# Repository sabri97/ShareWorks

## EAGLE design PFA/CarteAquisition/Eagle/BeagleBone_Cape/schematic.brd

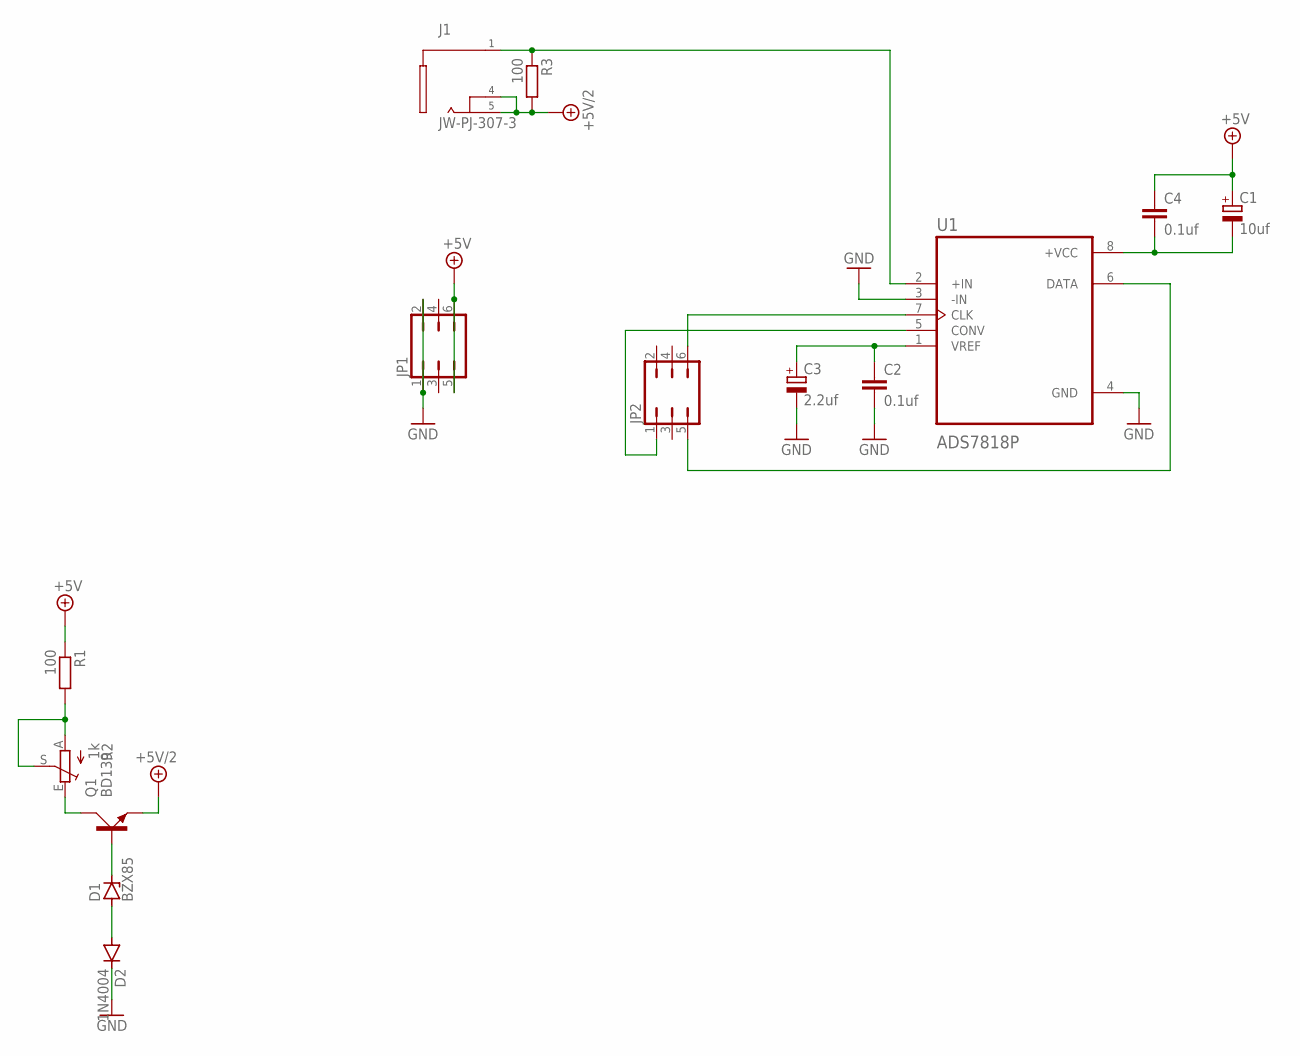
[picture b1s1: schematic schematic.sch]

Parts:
C1: 10uf; E3,5-8
C2, C4: 0.1uf; C050-030X075
C3: 2.2uf; E2,5-6
D1: BZX85; DO41Z10
D2: 1N4004; DO41-10
J1: JW-PJ-307-3; JW-PJ-307-X
JP1, JP2: JP3Q
Q1: BD139; TO126AV
R1, R3: 100; 0207/10
R2: 1k; CA9V
U1: ADS7818P; DIP794W45P254L959H508Q8

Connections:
+5V: C1.+, C4.1, JP1.5, JP1.6, R1.1
+5V/2: J1.P$4 (4), J1.P$5 (5), Q1.E, R3.2
GND: C2.2, C3.-, D2.C, JP1.1, JP1.2, U1.3 (-IN), U1.4 (GND)
unnamed: R1.2, R2.A, R2.S
unnamed: D1.A, D2.A
unnamed: D1.C, Q1.B
unnamed: Q1.C, R2.E
unnamed: JP2.6, U1.7 (CLK)
unnamed: J1.P$1 (1), R3.1, U1.2 (+IN)
unnamed: JP2.1, U1.5 (CONV)
unnamed: C2.1, C3.+, U1.1 (VREF)
unnamed: JP2.5, U1.6 (DATA)
unnamed: C1.-, C4.2, U1.8 (+VCC)

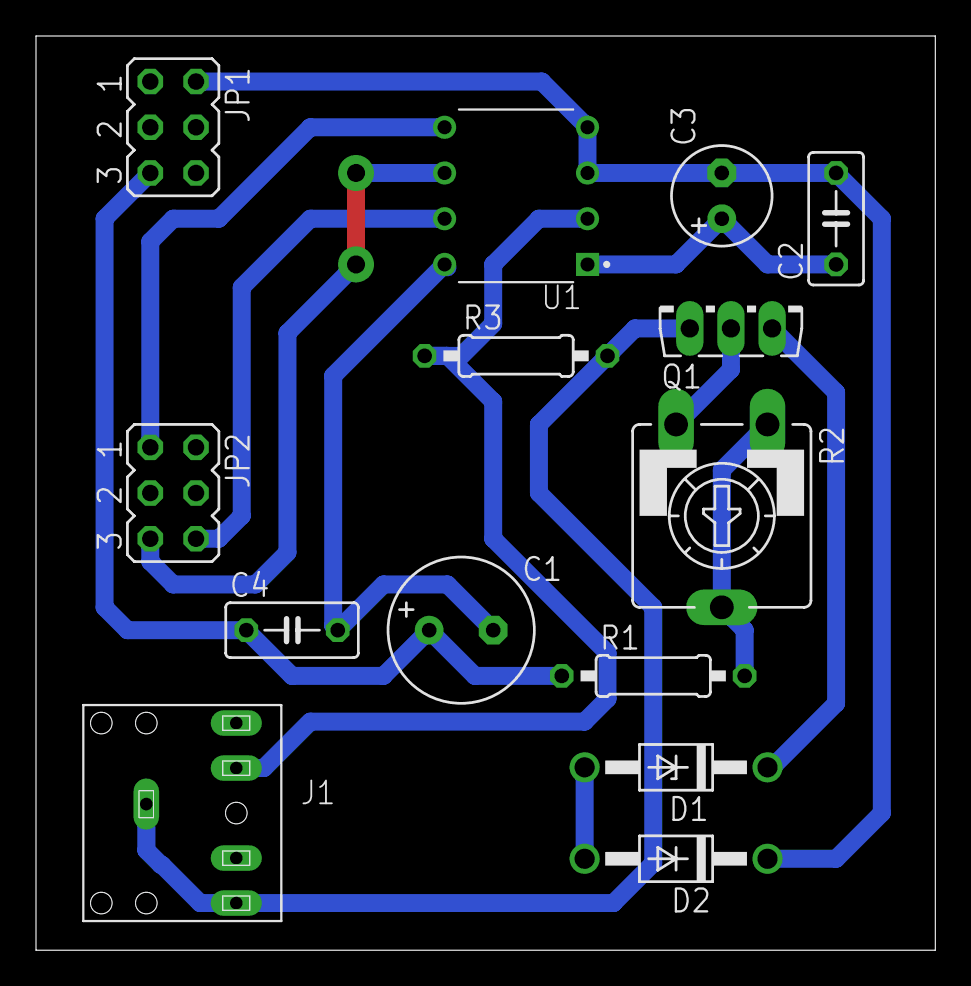
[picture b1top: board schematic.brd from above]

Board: 2 copper layers, 50.0 x 50.8 mm, 14 parts (0 on the bottom side), 13 nets.

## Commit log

2021-03-16 Addworks
2021-03-18 change
2021-03-18 Add files via upload
    BeagleBone cape (under eagle)
2021-03-20 addwork
2021-03-21 beaglebone cape update
2021-03-22 modify Latex Code C++
2021-03-24 rapport c++ modify
2021-04-07 hello
2021-04-07 MP_V6
